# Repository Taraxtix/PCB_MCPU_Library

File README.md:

# What is this
This repo is a collection of ready to use, prewired parts of PCB designs you can use inside MCPU applications

## How to use
- Inside your schematics, add a hierachical sheet linked to the .kicad_sch of the part you need
- Add all the hierarchical pins and connect it as you wish
- Inside you PCB editor, Click on "File -> Append Board", then select the kicad_pcb from the same directory as the kicad_sch
- After all prewired parts have been appended, Click on "Update PCB from Schematics" without forgetting to check the Option "Re-link footprints to schematics symbols based on their reference designators"

### WARNING
- You cannot use the same designators as I use in my parts (For that I'll only use designators starting from 100)
More precisly each part while have a use the following designator syntax: [Standard letter][Id of the part][Part number from 00 to 99]
By "Standard Letter" I mean C for capacitors, R for resistors, etc
I will keep a list of each part Id at the bottom of this read me

# Part Ids
- 1: Power_3V3_LDO

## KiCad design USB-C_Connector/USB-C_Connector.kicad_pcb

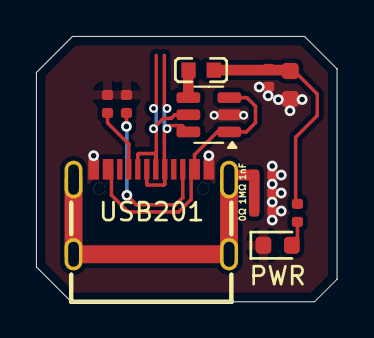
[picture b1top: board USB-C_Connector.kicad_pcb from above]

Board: 2 copper layers, 16.7 x 14.7 mm, 12 parts (0 on the bottom side), 10 nets.

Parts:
C201: 1nF; C_0402
C202: 100nF; C_0402
C203: 10uF; C_0603
D201: PWR; D_0603
L201: BLM18AG601SN1D; L0603
R201: 1MΩ; R_0402
R202: 0Ω; R_0402
R203: 120kΩ; R_0402
R204, R205: 5.1kΩ; R_0402
U201: TPD3S044; SOT-23-6
USB201: TYPE-C16PIN; USB-C-SMD_TYPE-C16PIN

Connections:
5V_USB: C202.1, C203.1, L201.2, R203.1
D+: U201.6 (D2), USB201.A6 (DP1), USB201.B6 (DP2)
D-: U201.5 (D1), USB201.A7 (DN1), USB201.B7 (DN2)
GND: C201.1, C202.2, C203.2, D201.1, R201.1, R202.1, R204.2, R205.2, U201.2 (GND), USB201.A1B12 (GND), USB201.B1A12 (GND)
unnamed: D201.2, R203.2
unnamed: L201.1, U201.4 (OUT)
unnamed: R204.1, USB201.A5 (CC1)
unnamed: R205.1, USB201.B5 (CC2)
SHIELD: C201.2, R201.2, R202.2, USB201.1 (SHELL), USB201.2 (SHELL), USB201.3 (SHELL), USB201.4 (SHELL)
VBUS_IN: U201.1 (EN), U201.3 (IN), USB201.A4B9 (VBUS), USB201.B4A9 (VBUS)

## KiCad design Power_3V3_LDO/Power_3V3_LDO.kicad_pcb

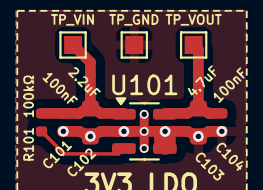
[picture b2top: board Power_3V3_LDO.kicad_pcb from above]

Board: 2 copper layers, 9 parts (0 on the bottom side), 4 nets.

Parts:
C101, C104: 100nF; C_0402
C102: 2.2uF; C_0603
C103: 4.7uF; C_0603
R101: 100kΩ; R_0402
TP101: TP_VIN; TestPoint_Pad_1.0x1.0mm
TP102: TP_VOUT; TestPoint_Pad_1.0x1.0mm
TP103: TP_GND; TestPoint_Pad_1.0x1.0mm
U101: TLV70033_SOT23-5; SOT-23-5

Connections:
EN: R101.2, U101.3 (EN)
GND: C101.2, C102.2, C103.2, C104.2, TP103.1, U101.2 (GND)
VIN: C101.1, C102.1, R101.1, TP101.1, U101.1 (IN)
VOUT: C103.1, C104.1, TP102.1, U101.5 (OUT)

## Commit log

2025-10-08 Ignore .lck files
2025-10-08 ignore more useless stuffs
2025-10-08 + Power_3V3_LDO_Island
2025-10-08 Adds MIT Licence and README
2025-10-09 Renamed Power_3V3_LDO (remove "Island")
    Technically everything should be an Island
2026-01-20 save
